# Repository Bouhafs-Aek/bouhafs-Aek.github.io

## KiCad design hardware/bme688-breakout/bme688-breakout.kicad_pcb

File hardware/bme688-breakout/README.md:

# BME688 4-in-1 Environmental Sensor Breakout

A KiCad 10 design for a host-agnostic breakout board around the **Bosch BME688**
(gas/VOC, humidity, pressure, temperature, LGA-8). It brings the sensor out on a
0.1" header that works with any I2C or SPI microcontroller at 3.3–5.5 V logic,
plus two Qwiic / STEMMA QT connectors for daisy-chaining on the 3.3 V side.

## A note on the part number

The request was for a "BLE688". No manufacturer sells a part by that name — it
does not appear in Bosch's, Nordic's, Fanstel's, Raytac's, EBYTE's or MOKO's
catalogues, nor in distributor search. The intended part was confirmed as the
Bosch **BME688**, which is what this design uses. If you actually wanted a
Bluetooth module, this is the wrong board and none of it carries over.

KiCad 10 ships a `Sensor:BME680` symbol but no BME688. The two parts are pin- and
package-compatible (Bosch LGA-8, 3.0 × 3.0 × 0.93 mm, identical pin assignment),
so `lib/BME688_Breakout.kicad_sym` restates the reviewed BME680 symbol as a
BME688 with the correct datasheet and description. The land pattern is KiCad's
own reviewed `Package_LGA:Bosch_LGA-8_3x3mm_P0.8mm_ClockwisePinNumbering`
(0.5 × 0.525 mm pads on 0.8 mm pitch), unmodified.

## Board

| | |
|---|---|
| Size | 38.10 × 27.94 mm (1.5" × 1.1") |
| Layers | 2, 1.6 mm FR4, B.Cu is a solid GND pour |
| KiCad | 10 (`kicad_sch` 20250901, `kicad_pcb` 20250907) |
| Input | 2.5–5.5 V on `VIN` → on-board AP2112K-3.3 LDO |
| Host logic | 3.3–5.5 V, set by `VIO`, level shifted on all four signals |
| Interfaces | I2C (default, 0x76) or SPI |
| Mounting | 4 × M2 (2.2 mm) at the corners |
| Min track / clearance | 0.25 mm / 0.20 mm (0.4 mm on power nets) |
| Vias | 0.6 mm pad / 0.3 mm drill |

## Pinout

### J1 — host header (2.54 mm, level-shifted to `VIO`)

| Pin | Name | Function |
|----:|------|----------|
| 1 | VIN | 2.5–5.5 V supply in |
| 2 | 3V3 | LDO output, ~350 mA spare |
| 3 | GND | |
| 4 | SCK | SPI clock / I2C SCL |
| 5 | SDI | SPI MOSI / I2C SDA |
| 6 | SDO | SPI MISO (unused in I2C) |
| 7 | CS | SPI chip select; leave open for I2C |
| 8 | GND | |
| 9 | VIO | host I/O reference, 3.3–5.5 V — see below |

### J2 — expansion header (2.54 mm, 3.3 V only)

| Pin | 1 | 2 | 3 | 4 |
|---|---|---|---|---|
| | 3V3 | GND | SDA | SCL |

### J3 / J4 — Qwiic / STEMMA QT (JST SH 1.0 mm, 3.3 V only)

Standard Qwiic order: 1 = GND, 2 = 3.3 V, 3 = SDA, 4 = SCL. The two connectors
are wired in parallel so boards can be chained. Shells are grounded.

Test pads TP1–TP4 expose the sensor-side SCK, SDI, SDO and CSB.

## Choosing the interface

**I2C — as manufactured, nothing to do.** R5 holds CSB high, so leaving `CS`
unconnected selects I2C. JP1 is bridged 1–2, giving address **0x76**. Cut 1–2
and bridge 2–3 for **0x77**.

**SPI — open JP1 completely first.** In SPI mode SDO is the sensor's *output*.
JP1 ties SDO hard to GND or 3V3 to set the I2C address, so driving SPI with JP1
still bridged would short that output. Open both sides of JP1, then drive `CS`.

> This is the one footgun in the design and it is deliberate: a hard tie is what
> makes the I2C address level unambiguous. A series resistor instead would form
> a divider against the host-side SDO pull-up and leave the address level
> floating around mid-rail. The trade is documented on the back silkscreen.

## Jumpers

| | Function | As manufactured |
|---|---|---|
| JP1 | I2C address / interface select | bridged 1–2 → 0x76 |
| JP2 | sensor-side I2C pull-ups (R1, R2) | bridged (pull-ups on) |
| JP3 | power LED | bridged (LED on) |
| JP4 | `VIO` → `VIN` | bridged (`VIO` = `VIN`) |

Cut **JP2** on every board but the first when chaining several over Qwiic, so
the bus only carries one pair of pull-ups. Cut **JP3** to save the LED's ~1 mA.
Cut **JP4** only if your host's I/O rail differs from `VIN` — then drive `VIO`
(J1 pin 9) from that rail instead.

## Design notes

**`VIO` is the host I/O rail, and it is not `VIN`.** The host-side pull-ups
reference `VIO`, which JP4 bridges to `VIN` as manufactured — so a single-rail
host (5 V board, 5 V logic; or 3.3 V board, 3.3 V logic) needs nothing done.
The split matters for the common mixed case: run the board from 5 V while
talking to a 3.3 V MCU (ESP32, RP2040, STM32) and pull-ups referenced to `VIN`
would idle all four signals at 5 V into 3.3 V GPIO. Cut JP4, feed `VIO` from
the host's 3.3 V rail, and the host side idles at 3.3 V.

**Why `VIO` bottoms out at 3.3 V.** Not a pull-up limit — a topology limit. A
BSS138 shifter needs its gate on the *lower* of the two rails, and here the
gate sits on the 3.3 V sensor rail. Take `VIO` below 3.3 V and the FET body
diode (anode at the source, i.e. the sensor side) forward-biases and pushes
roughly `VIO`+0.7 V back into the host. So 1.8 V logic is not supported by this
board and cannot be made to work by changing a resistor; it needs a dual-supply
translator such as a TXS0104E, with the I2C/SPI arbitration caveats below.

**Level shifting.** Four BSS138 + pull-up shifters (Q1–Q4), one per signal,
rather than a translator IC. The discrete shifter is bidirectional with no
direction pin, which matters here because SCK/SDI are shared between open-drain
I2C and push-pull SPI — an auto-direction part like the TXS0104E would have to
arbitrate against its own internal pull-ups, and a push-pull-only part like the
TXB0104 cannot do I2C at all. Cost is speed: with 10 kΩ pull-ups the SPI clock
is practical to a few MHz, not the BME688's 10 MHz maximum.

**SDO has no sensor-side pull-up.** Deliberate — see the SPI note above. The
host-side pull-up R7 draws `VIO`/10 kΩ through Q3 while JP1 holds SDO at GND in
I2C mode: ~330 µA at 3.3 V, ~500 µA at 5 V. That is negligible next to the
sensor's ~0.9 mA typical and ~3.7 mA heater current, but it does mean the board
is not a good fit for a µA-budget sleep design without cutting JP3 and
reworking R7.

**Nothing routes under a screw head.** The router treats each mounting hole as
a 3.8 mm keepout, not just a 2.2 mm drill, so no track or via passes beneath an
M2 head. Without it a signal track ran under H3 — a metal screw on a grounded
standoff would have shorted it to the B.Cu pour underneath. The pour itself is
left under the heads, which is harmless: it is ground, which is what a grounded
standoff would contact anyway.

**The via cost is deliberately steep.** B.Cu carries the pour, so every track
placed there cuts it. At a lower via cost the router took enough of the back
layer to fragment the pour into islands, stranding the ground pads that only
reached the plane through a via in the orphaned piece. Routing is now
~82% front-layer.

**Decoupling sits further out than ideal**, and the checker prints the real
figures: C1 is 3.29 mm from U1's VDD pad, C2 4.08 mm from VDDIO. Preferred
practice is under 2 mm, and the board is too dense to get there without shaving
courtyards to a few tens of microns. It is accepted rather than fixed because
the numbers say it does not matter here: ~4 mm of track is roughly 4 nH, and
against the BME688's heater step (~12 mA over microseconds) that is
L·dI/dt ≈ 50 nV of rail disturbance. The nearer cap is on VDD, which carries
the heater current, and the further one on VDDIO, which carries only I/O.

**Gas sensor placement.** The BME688's gas element is heated, and its readings
follow board temperature, so U1 sits at the top edge with the LDO diagonally
opposite ~13 mm away, and the LED and its resistor kept off that end. Thermal
isolation here is by placement only — there is no plane cutout under the sensor,
so expect the usual self-heating offset and calibrate it out.

**Handling.** The gas sensor is sensitive to siloxanes and solvent vapour: no
conformal coating, no silicone adhesives or sealants nearby, and follow Bosch's
reflow profile. Gas output needs Bosch's BSEC library and a burn-in period
before readings settle; the raw resistance is not an air-quality index.

## Left out on purpose

These are choices, not oversights, and each one is a way to damage the board or
be surprised by it:

- **No reverse-polarity protection on `VIN`.** A series Schottky would cost
  ~0.3 V, and at `VIN` = 2.5 V the LDO has no headroom to spare. Get `VIN` and
  `GND` backwards and you will kill the LDO and probably the sensor.
- **No ESD protection** on the header, Qwiic or test pads. Fine on a bench,
  not fine on a cable run to somewhere a person can touch.
- **`3V3` is an output, and Qwiic back-feeds it.** Driving `3V3` (J1 pin 2, J2
  pin 1, or either Qwiic) while the board is unpowered pushes current back into
  the LDO's output. Normal for Qwiic boards, still worth knowing.
- **No series resistors on the sensor-side bus.** With two Qwiic connectors it
  would be easy to build a chain long enough to want them.
- **Cutting JP2 on a standalone board kills the bus.** The BSS138 shifter needs
  pull-ups on both sides; JP2 removes the sensor-side pair, which only makes
  sense when another board on the chain provides them.

## Files

| Path | |
|---|---|
| `bme688-breakout.kicad_pro` | project, with design rules matching the checks |
| `bme688-breakout.kicad_sch` | schematic |
| `bme688-breakout.kicad_pcb` | board |
| `lib/BME688_Breakout.kicad_sym` | BME688 and VIN symbols |
| `doc/bom.csv` | BOM, 32 placements in 20 lines |
| `doc/board-preview.svg` | top and bottom render, pour as simulated |
| `scripts/design.py` | **the single source of truth**: parts, nets, placement |
| `scripts/verify.py` | the checks described below |

Standard footprints are referenced by their normal library names
(`Capacitor_SMD:C_0603_1608Metric` etc.) and resolve from your KiCad
installation; `scripts/fp_cache/` and `scripts/sym_cache/` hold copies from
KiCad 10.0.6 purely so the generators can run offline.

## Regenerating

`scripts/design.py` holds every part, net and coordinate; the schematic and
board are generated from it, so they cannot disagree about a connection. Edit
that file, then:

```sh
make          # regenerate symbols, schematic, board, project, preview + verify
make verify   # checks only
```

Routing is done by a small maze router (`scripts/router.py`) on a 0.1 mm grid
with a turn penalty, so tracks come out as straight runs and 45° corners. A full
regeneration takes about three minutes, most of it routing.

## What has been checked, and what has not

KiCad is not installed in the environment this was authored in, so the files
were written directly against the **KiCad 10** formats — `kicad_sch` 20250901,
`kicad_pcb` 20250907, `kicad_sym` 20251024 — every token form copied from the
demo project and libraries shipped with the KiCad **10.0.6** release. The
coordinate transforms were validated against a real KiCad project, and the
emitted token set was diffed against what KiCad 10.0.6 writes, to confirm no
KiCad 9 token survives (`hide` inside `effects`, `filled_areas_thickness`) and
that the KiCad 10 additions are present (`body_style`,
`duplicate_pin_numbers_are_jumpers`, `duplicate_pad_numbers_are_jumpers`,
`island_removal_mode`, per-side via `tenting`/`covering`/`plugging`).
`scripts/verify.py` re-parses the emitted files and checks:

- every pad's net matches `design.py`, and no pad is silently left floating
- **electrical connectivity** of all 15 nets, including a simulated pour fill —
  the GND pour is cut back around every foreign track, pad and via and
  flood-filled, so a pour split into islands is reported rather than assumed
  away (currently: all 19 GND items in a single region)
- copper-to-copper and hole-to-copper clearance ≥ 0.20 mm
- no footprint courtyard overlaps, all copper inside the board outline
- no silkscreen over pads
- the **schematic netlist matches `design.py` exactly**, pin for pin, and every
  unconnected pin carries a no-connect
- no overlapping symbols, everything on the A3 sheet

`scripts/dfm.py` then checks the fabrication rules the project file declares,
which nothing was testing until they were written:

- copper **stands back** ≥ 0.30 mm from the board edge (`min_copper_edge_clearance`)
  — not merely "is inside the outline", which a pad overhanging by 0.1 mm
  still satisfies
- hole-to-hole web ≥ 0.25 mm, annular ring ≥ 0.10 mm, drill ≥ 0.30 mm,
  track ≥ 0.20 mm, silkscreen text ≥ 0.40 mm
- no copper under a 3.8 mm M2 screw head
- silkscreen over a via, reported as a note rather than a warning because the
  board setup tents vias, so they sit under solder mask

All of the above passes. What has **not** happened:

- KiCad's own DRC and ERC have never run on these files
- no fab has looked at them, and no board has been built
- zones are defined but **not pre-filled** — **press `B` in pcbnew** on first
  open. This is deliberate rather than an omission: KiCad stores a zone's fill
  as `filled_polygon` and then uses it for rendering *and* for DRC
  connectivity rather than recomputing it on load, so writing an approximated
  fill here would leave DRC judging our approximation instead of a real fill.
  Our simulation is a 0.1 mm raster with square cut-backs and no thermal
  spokes; KiCad rounds the cut-backs, spokes same-net through-hole pads,
  applies `min_thickness` and removes islands. The bottom view of
  `doc/board-preview.svg` draws the simulated pour so you can see what `B`
  will produce — 85.8% of the zone outline stays copper, with all 19 GND items
  in a single region (the raster leaves one orphan island carrying no GND item,
  which is what `island_removal_mode` exists to drop) — but the authoritative
  fill is KiCad's
- reference designators are on **F.Fab**, not silkscreen: at 35 parts on 1.5" ×
  1.1" the silkscreen is used for functional labels instead
- SPI has not been validated at speed; treat the few-MHz figure as an estimate
  from the pull-up RC, not a measurement

Open it in KiCad, fill zones, run DRC and ERC, and review the placement against
your enclosure before ordering anything.

## Licence and attribution

Symbols and footprints are derived from the official KiCad libraries
(CC-BY-SA 4.0 with the library exception, which permits use in a design without
imposing terms on the design). See `scripts/fp_cache/README.md`.

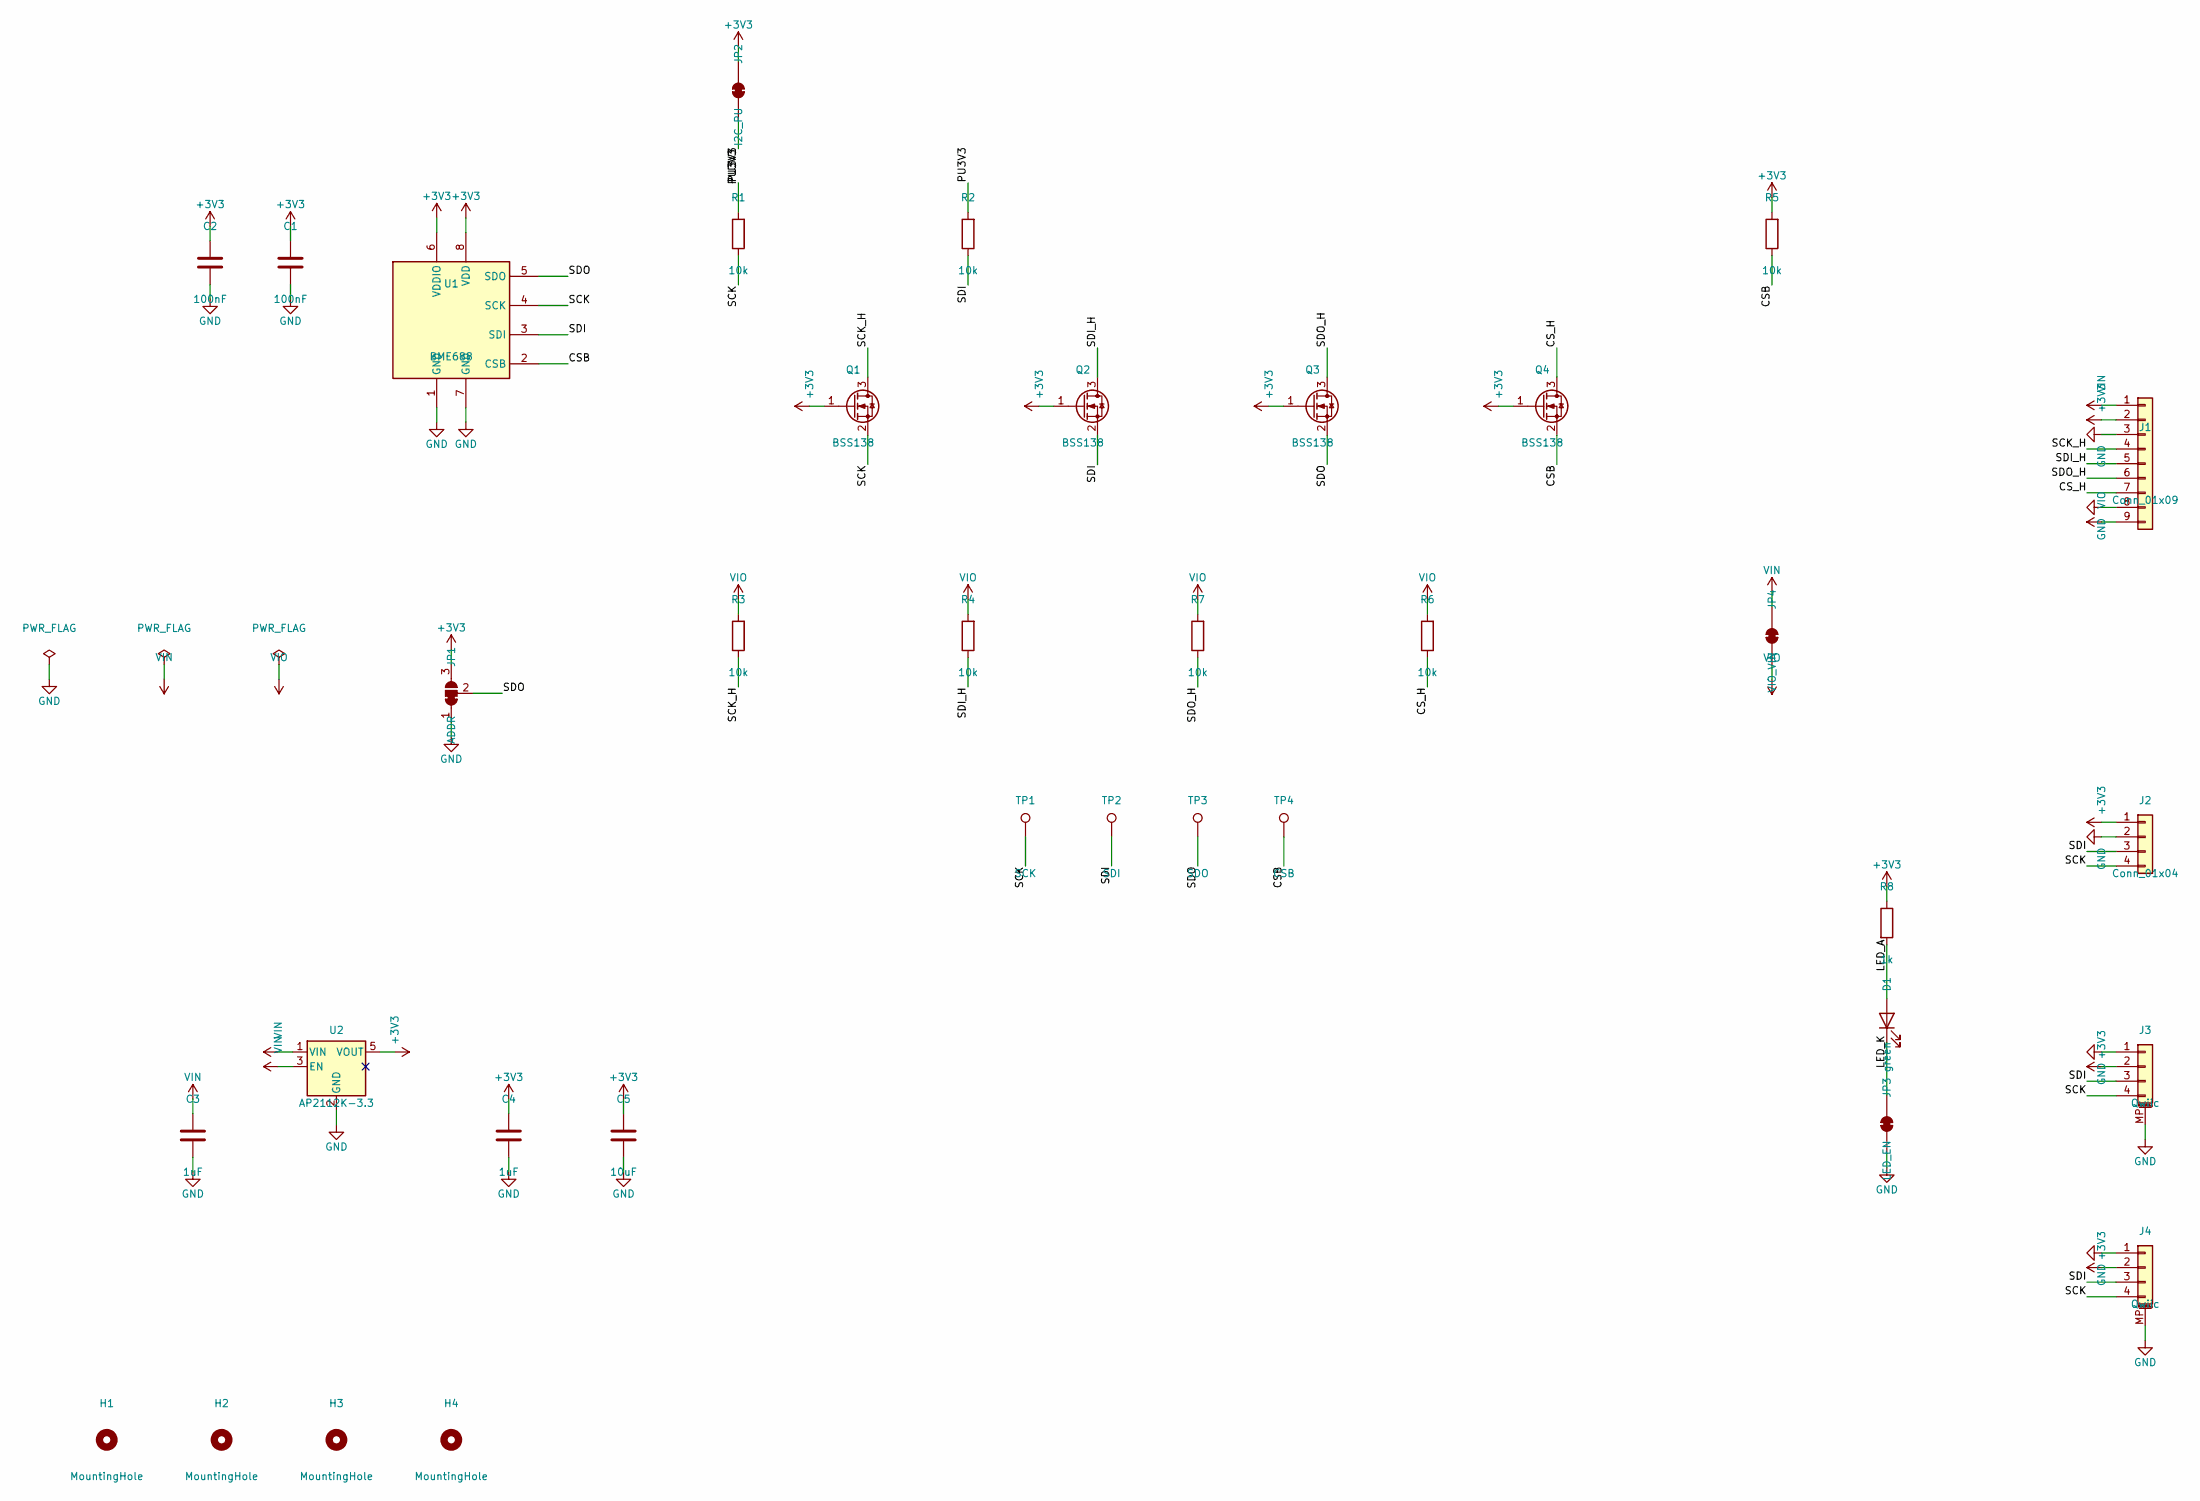
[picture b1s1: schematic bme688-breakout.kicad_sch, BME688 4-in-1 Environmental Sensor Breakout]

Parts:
C1, C2: 100nF; C_0603_1608Metric
C3, C4: 1uF; C_0603_1608Metric
C5: 10uF; C_0603_1608Metric
D1: green; LED_0603_1608Metric
H1, H2, H3, H4: MountingHole; MountingHole_2.2mm_M2
J1: Conn_01x09; PinHeader_1x09_P2.54mm_Vertical
J2: Conn_01x04; PinHeader_1x04_P2.54mm_Vertical
J3, J4: Qwiic; JST_SH_SM04B-SRSS-TB_1x04-1MP_P1.00mm_Horizontal
JP1: ADDR; SolderJumper-3_P1.3mm_Bridged12_RoundedPad1.0x1.5mm
JP2: I2C_PU; SolderJumper-2_P1.3mm_Bridged_RoundedPad1.0x1.5mm
JP3: LED_EN; SolderJumper-2_P1.3mm_Bridged_RoundedPad1.0x1.5mm
JP4: VIO_VIN; SolderJumper-2_P1.3mm_Bridged_RoundedPad1.0x1.5mm
Q1, Q2, Q3, Q4: BSS138; SOT-23
R1, R2, R3, R4, R5, R6, R7: 10k; R_0603_1608Metric
R8: 1k; R_0603_1608Metric
TP1: SCK; TestPoint_Pad_D1.0mm
TP2: SDI; TestPoint_Pad_D1.0mm
TP3: SDO; TestPoint_Pad_D1.0mm
TP4: CSB; TestPoint_Pad_D1.0mm
U1: BME688; Bosch_LGA-8_3x3mm_P0.8mm_ClockwisePinNumbering
U2: AP2112K-3.3; SOT-23-5

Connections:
+3V3: C1.1, C2.1, C4.1, C5.1, J1.2, J2.1, J3.2, J4.2, JP1.3, JP2.1, Q1.1, Q2.1, Q3.1, Q4.1, R5.2, R8.1, U1.6, U1.8, U2.5
CSB: Q4.2, R5.1, TP4.1, U1.2
CS_H: J1.7, Q4.3, R6.1
GND: C1.2, C2.2, C3.2, C4.2, C5.2, J1.3, J1.8, J2.2, J3.1, J3.MP, J4.1, J4.MP, JP1.1, JP3.2, U1.1, U1.7, U2.2
LED_A: D1.2, R8.2
LED_K: D1.1, JP3.1
PU3V3: JP2.2, R1.2, R2.2
SCK: J2.4, J3.4, J4.4, Q1.2, R1.1, TP1.1, U1.4
SCK_H: J1.4, Q1.3, R3.1
SDI: J2.3, J3.3, J4.3, Q2.2, R2.1, TP2.1, U1.3
SDI_H: J1.5, Q2.3, R4.1
SDO: JP1.2, Q3.2, TP3.1, U1.5
SDO_H: J1.6, Q3.3, R7.1
VIN: C3.1, J1.1, JP4.1, U2.1, U2.3
VIO: J1.9, JP4.2, R3.2, R4.2, R6.2, R7.2

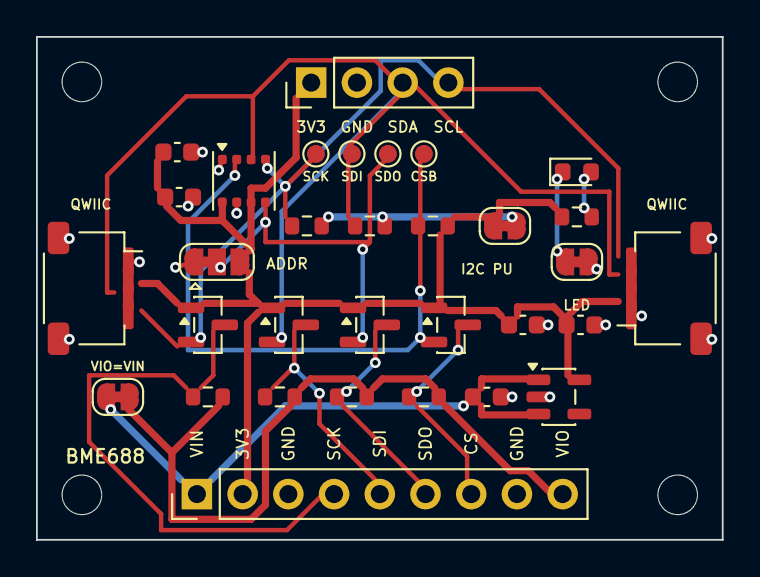
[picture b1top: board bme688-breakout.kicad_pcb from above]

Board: 2 copper layers, 38.1 x 27.9 mm, 36 parts (0 on the bottom side), 15 nets.

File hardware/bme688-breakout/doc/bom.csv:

Refs,Qty,Value,Footprint,Notes
C1 C2,2,100nF,C_0603_1608Metric,C1: VDD decoupling; C2: VDDIO decoupling
C3 C4,2,1uF,C_0603_1608Metric,C3: LDO input; C4: LDO output
C5,1,10uF,C_0603_1608Metric,3.3V bulk
D1,1,green,LED_0603_1608Metric,Power indicator
J1,1,Conn_01x09,PinHeader_1x09_P2.54mm_Vertical,"Host header, 2.54mm"
J2,1,Conn_01x04,PinHeader_1x04_P2.54mm_Vertical,"3.3V I2C expansion header, 2.54mm"
J3 J4,2,Qwiic,JST_SH_SM04B-SRSS-TB_1x04-1MP_P1.00mm_Horizontal,"J3: Qwiic / STEMMA QT, JST SH 1.0mm"
JP1,1,ADDR,SolderJumper-3_P1.3mm_Bridged12_RoundedPad1.0x1.5mm,"I2C address: 1-2 = 0x76 (default), 2-3 = 0x77, open = SPI"
JP2,1,I2C_PU,SolderJumper-2_P1.3mm_Bridged_RoundedPad1.0x1.5mm,Sensor-side I2C pull-ups; cut on daisy-chained boards
JP3,1,LED_EN,SolderJumper-2_P1.3mm_Bridged_RoundedPad1.0x1.5mm,Cut to disable the power LED
JP4,1,VIO_VIN,SolderJumper-2_P1.3mm_Bridged_RoundedPad1.0x1.5mm,Ties VIO to VIN; cut when the host I/O rail differs
Q1 Q2 Q3 Q4,4,BSS138,SOT-23,"Q1: Level shifter, SCK/SCL; Q2: Level shifter, SDI/SDA; Q3: Level shifter, SDO/MISO; Q4: Level shifter, CSB/CS"
R1 R2 R3 R4 R5 R6 R7,7,10k,R_0603_1608Metric,"R1: SCL pull-up, sensor side; R2: SDA pull-up, sensor side; R3: SCK/SCL pull-up, host side; R4: SDI/SDA pull-up, host side; R5: CSB pull-up: selects I2C when CS is left open; R6: CS pull-up, host side; R7: SDO/MISO pull-up, host side"
R8,1,1k,R_0603_1608Metric,Power LED series resistor
TP1,1,SCK,TestPoint_Pad_D1.0mm,"Test pad, sensor-side SCK/SCL"
TP2,1,SDI,TestPoint_Pad_D1.0mm,"Test pad, sensor-side SDI/SDA"
TP3,1,SDO,TestPoint_Pad_D1.0mm,"Test pad, sensor-side SDO"
TP4,1,CSB,TestPoint_Pad_D1.0mm,"Test pad, sensor-side CSB"
U1,1,BME688,Bosch_LGA-8_3x3mm_P0.8mm_ClockwisePinNumbering,"Bosch 4-in-1 gas/humidity/pressure/temperature sensor, LGA-8"
U2,1,AP2112K-3.3,SOT-23-5,"3.3V 600mA LDO, 2.5-6V input"

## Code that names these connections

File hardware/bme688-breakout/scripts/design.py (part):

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
Interface notes that drive the netlist:
  * BME688 picks its interface from CSB: high = I2C, low/toggling = SPI.
    R5 holds CSB high so an unconnected CS pin means I2C.
  * In I2C mode SDO is the address select pin: GND = 0x76, VDDIO = 0x77.
    JP1 ties it, and is bridged 1-2 (0x76) as manufactured.
  * Q1..Q4 are BSS138 bidirectional level shifters, one per signal, so the
    0.1" header works with 3.3-5.5V host logic while the sensor side stays at
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GND_NET = 'GND'

# Silkscreen pin labels for the two 2.54mm headers.
J1_LABELS = ['VIN', '3V3', 'GND', 'SCK', 'SDI', 'SDO', 'CS', 'GND', 'VIO']
J2_LABELS = ['3V3', 'GND', 'SDA', 'SCL']


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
